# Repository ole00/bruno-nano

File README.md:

# bruno-nano
Arduino UNO breakout board for NANO style MCU boards

This PCB allows you to experiment with various Arduino UNO shields while using an Arduino NANO style
board. The picture above uses a cheap LGT8F328P based NANO board.

NANO has - compared to UNO - two extra pins: A6 and A7. These are exposed to UNO pin header, next to
IOREF pin.

Capacitor C1 is a bypass capacitor for 5V rail, use 10 to 47uF capacitor or leave the footprint unpopulated.
Capacitor C2 is a bypass capacitor for 3.3V rail, use 10 to 47uF capacitor or leave the footprint unpopulated.

PCB version 1.1 (Rev 2) allows to select 5V or 3.3V IOREF voltage by using a jumper. Ensure your
IOREF voltage selection matches the MCU VCC. That is, if the MCU operates on 3.3V then select 3.3V IOREF
and if the MCU operates on 5V then select 5V IOREF. If unsure, then do not populate IOREF jumper at all.
Chances are the shield will not need the IOREF pin. Note that IOREF jumper does not magically
make your board 5V or 3.3V tolerant - IOREF pin is only used for IO voltage indication.

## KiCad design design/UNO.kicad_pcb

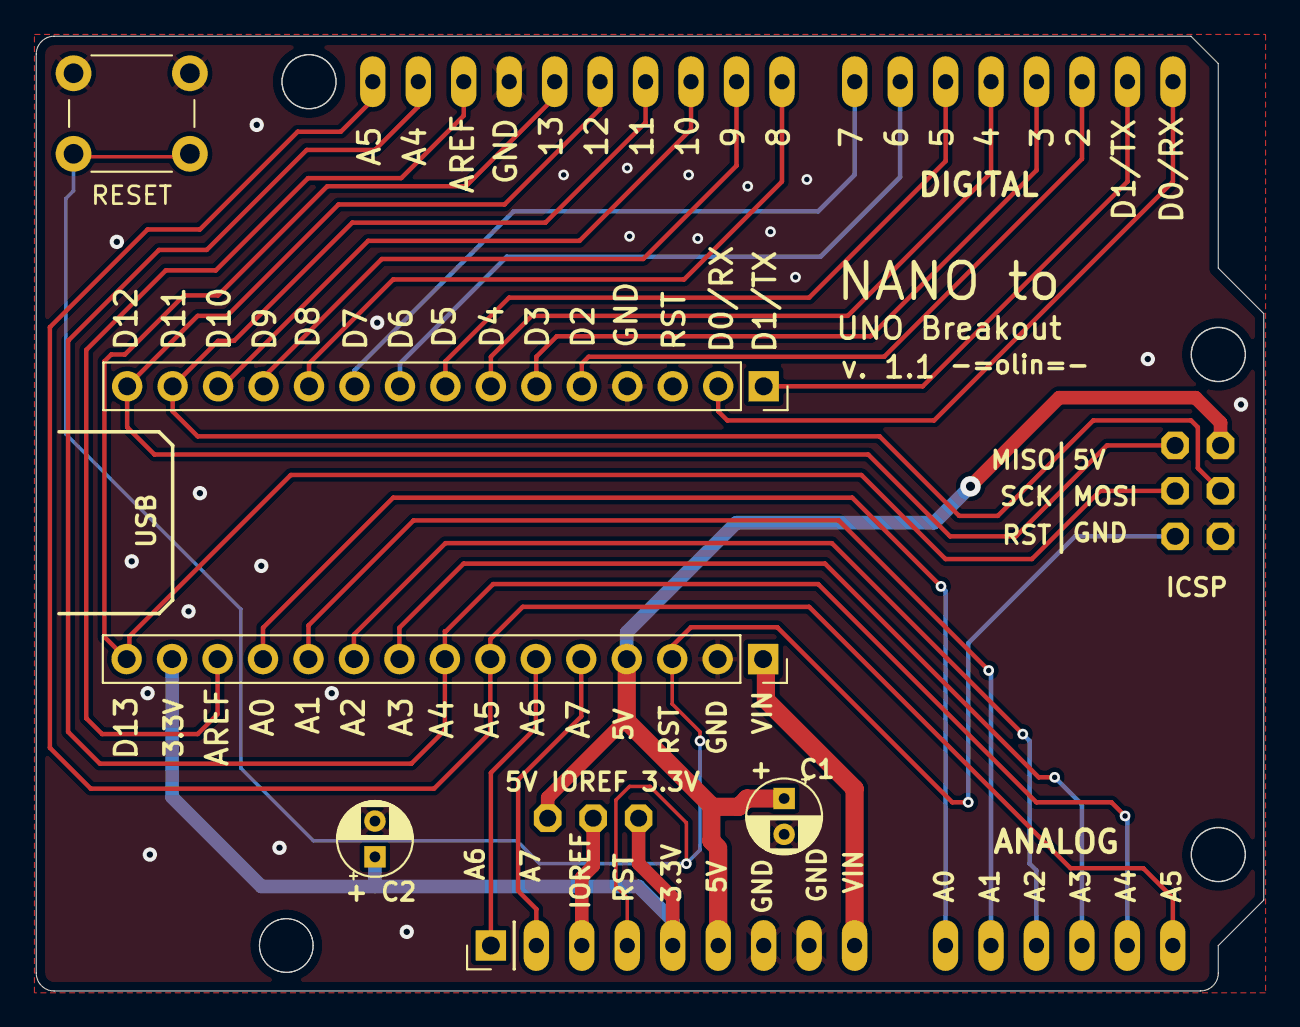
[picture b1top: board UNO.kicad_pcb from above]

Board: 2 copper layers, 68.6 x 53.3 mm, 5 parts (0 on the bottom side), 8 nets.

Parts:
A6: PinHeader_1x01_P2.54mm_Vertical
ANALOG: -; 1X14_
DIGITAL: -; 1X18_
RESET: SW_PUSH_6mm_H5mm
SPI1: -; 2X03

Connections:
+5V: ANALOG.5, SPI1.2
GND: ANALOG.6, ANALOG.7, DIGITAL.15, RESET.1, SPI1.6
PD4: ANALOG.13, DIGITAL.17
PD5: ANALOG.14, DIGITAL.18
PE0: DIGITAL.12, SPI1.4
PE1: DIGITAL.13, SPI1.1
PE2: DIGITAL.14, SPI1.3
TRG_RST: ANALOG.3, RESET.2, SPI1.5
